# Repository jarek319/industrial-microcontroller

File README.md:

# industrial-microcontroller
A familiar platform designed for robust and unpredictable environments

I really like this project. I worked at a museum fabricator for a while, working on their electronic internals. I had an awesome time and I learned a lot about real-world applications and how to make a design that works perfectly on a lab bench work perfectly after being shipped around the world, plugged into the wrong power supply, kicked repeatedly and left in baking heat and 100% humidity.

Lots of isolation.

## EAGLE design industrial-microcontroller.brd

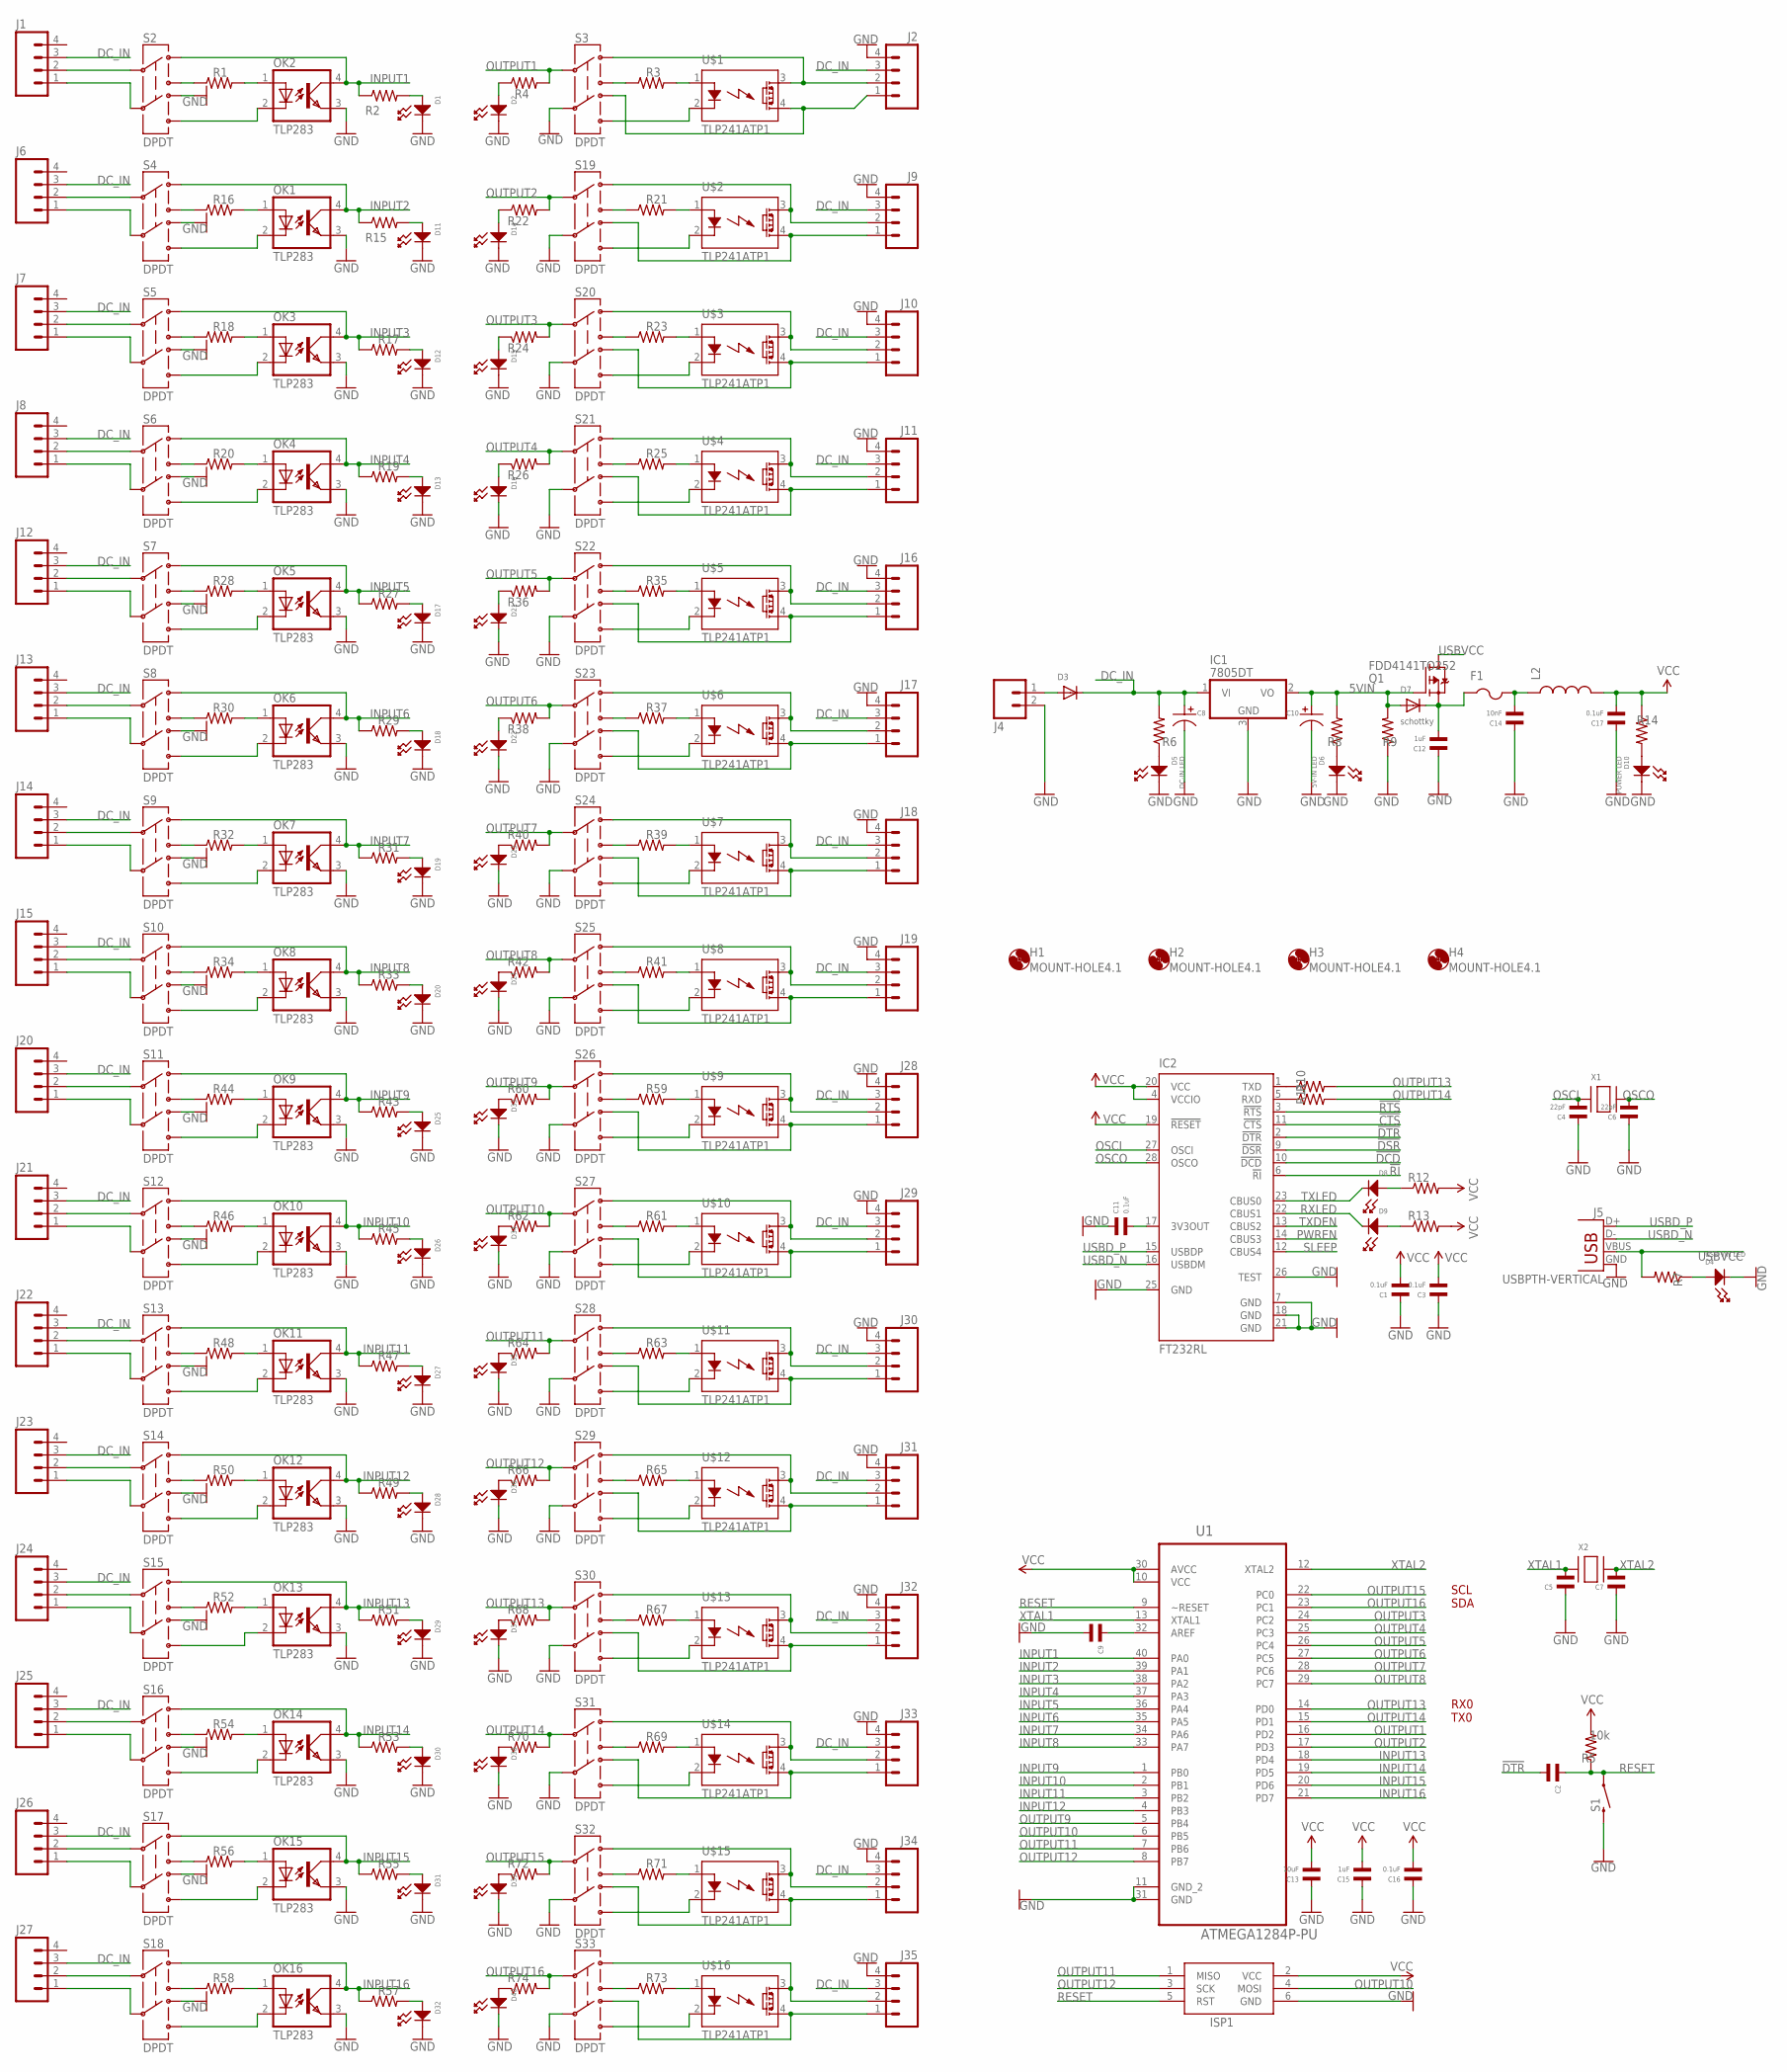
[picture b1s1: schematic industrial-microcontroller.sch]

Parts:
C1, C3, C11, C16, C17: 0.1uF; C0805
C2, C5, C7, C9: CAPACITOR_NP_0805; C0805
C4, C6: 22pF; C0805
C8, C10: CAPACITOR_P_10MM; CP10MM
C12, C15: 1uF; C0805
C13: 10uF; C0805
C14: 10nF; C0805
D1, D2, D8, D9, D11, D12, D13, D14, D15, D16, D17, D18, D19, D20, D21, D22, D23, D24, D25, D26, D27, D28, D29, D30, D31, D32, D33, D34, D35, D36, D37, D38, D39, D40: LED_SINGLE-0805; LED0805
D3: DIODESMA; SMADIODE
D4: USB-VIN LED; LED0805
D5: DC-IN LED; LED0805
D6: 5V-IN LED; LED0805
D7: schottky; SMADIODE
D10: POWER LED; LED0805
F1: PTCFUSE-1812; 1812
H1, H2, H3, H4: MOUNT-HOLE4.1; 4,1
IC1: 7805DT; TO252
IC2: FT232RL; SSOP28
ISP1: AVRISP-BOX
J1, J2, J6, J7, J8, J9, J10, J11, J12, J13, J14, J15, J16, J17, J18, J19, J20, J21, J22, J23, J24, J25, J26, J27, J28, J29, J30, J31, J32, J33, J34, J35: M04POLAR; MOLEX-1X4
J4: M02POLAR; MOLEX-1X2
J5: USBPTH-VERTICAL; USB-B-PTH-VERTICAL
L2: INDUCTORCR75_V2; CR75_V2
OK1, OK2, OK3, OK4, OK5, OK6, OK7, OK8, OK9, OK10, OK11, OK12, OK13, OK14, OK15, OK16: TLP283; MINI-FLAT-4
Q1: FDD4141TO252; TO252
R1, R2, R3, R4, R6, R7, R8, R9, R10, R11, R12, R13, R14, R15, R16, R17, R18, R19, R20, R21, R22, R23, R24, R25, R26, R27, R28, R29, R30, R31, R32, R33, R34, R35, R36, R37, R38, R39, R40, R41, R42, R43, R44, R45, R46, R47, R48, R49, R50, R51, R52, R53, R54, R55, R56, R57, R58, R59, R60, R61, R62, R63, R64, R65, R66, R67, R68, R69, R70, R71, R72, R73, R74: RESISTOR_0805; R0805
R5: 10k; R0805
S1: SWITCH-MOMENTARY-212MM; TACTILE-PTH-12MM
S2, S3, S4, S5, S6, S7, S8, S9, S10, S11, S12, S13, S14, S15, S16, S17, S18, S19, S20, S21, S22, S23, S24, S25, S26, S27, S28, S29, S30, S31, S32, S33: DPDT; JS202011JCON
U1: ATMEGA1284P-PU; DIP254P1524X483-40
U$1, U$2, U$3, U$4, U$5, U$6, U$7, U$8, U$9, U$10, U$11, U$12, U$13, U$14, U$15, U$16: TLP241ATP1; TLP241A-TP1
X1, X2: XTAL-3.2X1.5; XTAL3215

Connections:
5VIN: C10.P$1, D7.A, IC1.2 (VO), Q1.1 (G), R8.P$2, R9.P$2
!CTS: IC2.11 (!CTS)
!DCD: IC2.10 (!DCD)
!DSR: IC2.9 (!DSR)
!DTR: C2.P$2, IC2.2 (!DTR)
!RI: IC2.6 (!RI)
!RTS: IC2.3 (!RTS)
DC_IN: C8.P$1, D3.C, IC1.1 (VI), J1.3, J2.3, J6.3, J7.3, J8.3, J9.3, J10.3, J11.3, J12.3, J13.3, J14.3, J15.3, J16.3, J17.3, J18.3, J19.3, J20.3, J21.3, J22.3, J23.3, J24.3, J25.3, J26.3, J27.3, J28.3, J29.3, J30.3, J31.3, J32.3, J33.3, J34.3, J35.3, R6.P$2
GND: C1.P$1, C3.P$1, C4.P$1, C5.P$1, C6.P$1, C7.P$1, C8.P$2, C9.P$2, C10.P$2, C11.P$1, C12.P$1, C13.P$1, C14.P$1, C15.P$1, C16.P$1, C17.P$1, D1.CATHODE, D2.CATHODE, D4.CATHODE, D5.CATHODE, D6.CATHODE, D10.CATHODE, D11.CATHODE, D12.CATHODE, D13.CATHODE, D14.CATHODE, D15.CATHODE, D16.CATHODE, D17.CATHODE, D18.CATHODE, D19.CATHODE, D20.CATHODE, D21.CATHODE, D22.CATHODE, D23.CATHODE, D24.CATHODE, D25.CATHODE, D26.CATHODE, D27.CATHODE, D28.CATHODE, D29.CATHODE, D30.CATHODE, D31.CATHODE, D32.CATHODE, D33.CATHODE, D34.CATHODE, D35.CATHODE, D36.CATHODE, D37.CATHODE, D38.CATHODE, D39.CATHODE, D40.CATHODE, IC1.3 (GND), IC2.7 (GND), IC2.18 (GND), IC2.21 (GND), IC2.25 (GND), IC2.26 (TEST), ISP1.6 (GND), J2.4, J4.2, J5.GND, J9.4, J10.4, J11.4, J16.4, J17.4, J18.4, J19.4, J28.4, J29.4, J30.4, J31.4, J32.4, J33.4, J34.4, J35.4, OK1.3 (EMIT), OK2.3 (EMIT), OK3.3 (EMIT), OK4.3 (EMIT), OK5.3 (EMIT), OK6.3 (EMIT), OK7.3 (EMIT), OK8.3 (EMIT), OK9.3 (EMIT), OK10.3 (EMIT), OK11.3 (EMIT), OK12.3 (EMIT), OK13.3 (EMIT), OK14.3 (EMIT), OK15.3 (EMIT), OK16.3 (EMIT), R9.P$1, S1.3 (2), S2.4, S3.5, S4.4, S5.4, S6.4, S7.4, S8.4, S9.4, S10.4, S11.4, S12.4, S13.4, S14.4, S15.4, S16.4, S17.4, S18.4, S19.5, S20.5, S21.5, S22.5, S23.5, S24.5, S25.5, S26.5, S27.5, S28.5, S29.5, S30.5, S31.5, S32.5, S33.5, U1.11 (GND_2), U1.31 (GND)
INPUT1: OK2.4 (COL), R2.P$1, S2.1, U1.40 (PA0)
INPUT2: OK1.4 (COL), R15.P$1, S4.1, U1.39 (PA1)
INPUT3: OK3.4 (COL), R17.P$1, S5.1, U1.38 (PA2)
INPUT4: OK4.4 (COL), R19.P$1, S6.1, U1.37 (PA3)
INPUT5: OK5.4 (COL), R27.P$1, S7.1, U1.36 (PA4)
INPUT6: OK6.4 (COL), R29.P$1, S8.1, U1.35 (PA5)
INPUT7: OK7.4 (COL), R31.P$1, S9.1, U1.34 (PA6)
INPUT8: OK8.4 (COL), R33.P$1, S10.1, U1.33 (PA7)
INPUT9: OK9.4 (COL), R43.P$1, S11.1, U1.1 (PB0)
INPUT10: OK10.4 (COL), R45.P$1, S12.1, U1.2 (PB1)
INPUT11: OK11.4 (COL), R47.P$1, S13.1, U1.3 (PB2)
INPUT12: OK12.4 (COL), R49.P$1, S14.1, U1.4 (PB3)
INPUT13: OK13.4 (COL), R51.P$1, S15.1, U1.18 (PD4)
INPUT14: OK14.4 (COL), R53.P$1, S16.1, U1.19 (PD5)
INPUT15: OK15.4 (COL), R55.P$1, S17.1, U1.20 (PD6)
INPUT16: OK16.4 (COL), R57.P$1, S18.1, U1.21 (PD7)
unnamed: D5.ANODE, R6.P$1
unnamed: D1.ANODE, R2.P$2
unnamed: D6.ANODE, R8.P$1
unnamed: C14.P$2, F1.2, L2.P$1 (1)
unnamed: D10.ANODE, R14.P$2
unnamed: D3.A, J4.1
unnamed: D4.ANODE, R7.P$1
unnamed: D11.ANODE, R15.P$2
unnamed: R18.P$1, S5.3
unnamed: R3.P$2, U$1.1 (A)
unnamed: R20.P$1, S6.3
unnamed: OK1.1 (A), R16.P$2
unnamed: D12.ANODE, R17.P$2
unnamed: R28.P$1, S7.3
unnamed: R30.P$1, S8.3
unnamed: OK3.1 (A), R18.P$2
unnamed: D2.ANODE, R4.P$1
unnamed: D13.ANODE, R19.P$2
unnamed: R32.P$1, S9.3
unnamed: OK2.2 (C), S2.6
unnamed: R34.P$1, S10.3
unnamed: OK4.1 (A), R20.P$2
unnamed: R1.P$1, S2.3
unnamed: D14.ANODE, R22.P$1
unnamed: J9.2, S19.1, U$2.3 (DS1)
unnamed: OK2.1 (A), R1.P$2
unnamed: J9.1, S19.4, U$2.4 (DS2)
unnamed: R21.P$2, U$2.1 (A)
unnamed: D15.ANODE, R24.P$1
unnamed: J10.2, S20.1, U$3.3 (DS1)
unnamed: J10.1, S20.4, U$3.4 (DS2)
unnamed: R23.P$2, U$3.1 (A)
unnamed: D16.ANODE, R26.P$1
unnamed: J11.2, S21.1, U$4.3 (DS1)
unnamed: J2.2, S3.1, U$1.3 (DS1)
unnamed: J11.1, S21.4, U$4.4 (DS2)
unnamed: R25.P$2, U$4.1 (A)
unnamed: J2.1, S3.4, U$1.4 (DS2)
unnamed: D17.ANODE, R27.P$2
unnamed: R44.P$1, S11.3
unnamed: R46.P$1, S12.3
unnamed: OK5.1 (A), R28.P$2
unnamed: D18.ANODE, R29.P$2
unnamed: R48.P$1, S13.3
unnamed: R50.P$1, S14.3
unnamed: OK6.1 (A), R30.P$2
unnamed: D19.ANODE, R31.P$2
unnamed: R52.P$1, S15.3
unnamed: R54.P$1, S16.3
unnamed: C11.P$2, IC2.17 (3V3OUT)
unnamed: OK7.1 (A), R32.P$2
unnamed: D20.ANODE, R33.P$2
unnamed: D8.ANODE, R12.P$1
unnamed: R56.P$1, S17.3
unnamed: D9.ANODE, R13.P$1
unnamed: IC2.1 (TXD), R10.P$1
unnamed: IC2.5 (RXD), R11.P$1
unnamed: R58.P$1, S18.3
unnamed: OK8.1 (A), R34.P$2
unnamed: C9.P$1, U1.32 (AREF)
unnamed: D21.ANODE, R36.P$1
unnamed: J16.2, S22.1, U$5.3 (DS1)
unnamed: J16.1, S22.4, U$5.4 (DS2)
unnamed: C12.P$2, D7.C, F1.1, Q1.2 (S)
unnamed: R35.P$2, U$5.1 (A)
unnamed: D22.ANODE, R38.P$1
unnamed: J17.2, S23.1, U$6.3 (DS1)
unnamed: J17.1, S23.4, U$6.4 (DS2)
unnamed: R37.P$2, U$6.1 (A)
unnamed: D23.ANODE, R40.P$1
unnamed: J18.2, S24.1, U$7.3 (DS1)
unnamed: J18.1, S24.4, U$7.4 (DS2)
unnamed: R39.P$2, U$7.1 (A)
unnamed: D24.ANODE, R42.P$1
unnamed: J19.2, S25.1, U$8.3 (DS1)
unnamed: J19.1, S25.4, U$8.4 (DS2)
unnamed: R41.P$2, U$8.1 (A)
unnamed: D25.ANODE, R43.P$2
unnamed: R16.P$1, S4.3
unnamed: J6.2, S4.2
unnamed: OK9.1 (A), R44.P$2
unnamed: D26.ANODE, R45.P$2
unnamed: J6.1, S4.5
unnamed: J7.1, S5.5
unnamed: OK10.1 (A), R46.P$2
unnamed: D27.ANODE, R47.P$2
unnamed: J7.2, S5.2
unnamed: OK1.2 (C), S4.6
unnamed: OK11.1 (A), R48.P$2
unnamed: D28.ANODE, R49.P$2
unnamed: OK3.2 (C), S5.6
unnamed: J8.2, S6.2
unnamed: OK12.1 (A), R50.P$2
unnamed: D29.ANODE, R51.P$2
unnamed: J8.1, S6.5
unnamed: OK4.2 (C), S6.6
unnamed: OK13.1 (A), R52.P$2
unnamed: D30.ANODE, R53.P$2
unnamed: J12.2, S7.2
unnamed: J12.1, S7.5
unnamed: OK14.1 (A), R54.P$2
unnamed: D31.ANODE, R55.P$2
unnamed: OK5.2 (C), S7.6
unnamed: OK6.2 (C), S8.6
unnamed: OK15.1 (A), R56.P$2
unnamed: D32.ANODE, R57.P$2
unnamed: J13.2, S8.2
unnamed: J13.1, S8.5
unnamed: OK16.1 (A), R58.P$2
unnamed: D33.ANODE, R60.P$1
unnamed: J28.2, S26.1, U$9.3 (DS1)
unnamed: J28.1, S26.4, U$9.4 (DS2)
unnamed: R59.P$2, U$9.1 (A)
unnamed: D34.ANODE, R62.P$1
unnamed: J29.2, S27.1, U$10.3 (DS1)
unnamed: J29.1, S27.4, U$10.4 (DS2)
unnamed: R61.P$2, U$10.1 (A)
unnamed: D35.ANODE, R64.P$1
unnamed: J30.2, S28.1, U$11.3 (DS1)
unnamed: J30.1, S28.4, U$11.4 (DS2)
unnamed: R63.P$2, U$11.1 (A)
unnamed: D36.ANODE, R66.P$1
unnamed: J31.2, S29.1, U$12.3 (DS1)
unnamed: J31.1, S29.4, U$12.4 (DS2)
unnamed: R65.P$2, U$12.1 (A)
unnamed: D37.ANODE, R68.P$1
unnamed: J32.2, S30.1, U$13.3 (DS1)
unnamed: J32.1, S30.4, U$13.4 (DS2)
unnamed: R67.P$2, U$13.1 (A)
unnamed: D38.ANODE, R70.P$1
unnamed: J33.2, S31.1, U$14.3 (DS1)
unnamed: J33.1, S31.4, U$14.4 (DS2)
unnamed: R69.P$2, U$14.1 (A)
unnamed: D39.ANODE, R72.P$1
unnamed: J34.2, S32.1, U$15.3 (DS1)
unnamed: J34.1, S32.4, U$15.4 (DS2)
unnamed: R71.P$2, U$15.1 (A)
unnamed: D40.ANODE, R74.P$1
unnamed: J35.2, S33.1, U$16.3 (DS1)
unnamed: J35.1, S33.4, U$16.4 (DS2)
unnamed: R73.P$2, U$16.1 (A)
unnamed: J1.2, S2.2
unnamed: J1.1, S2.5
unnamed: R3.P$1, S3.3
unnamed: S3.6, U$1.2 (K)
unnamed: J14.2, S9.2
unnamed: J14.1, S9.5
unnamed: OK7.2 (C), S9.6
unnamed: J15.2, S10.2
unnamed: J15.1, S10.5
unnamed: OK8.2 (C), S10.6
unnamed: J20.2, S11.2
unnamed: J20.1, S11.5
unnamed: OK9.2 (C), S11.6
unnamed: OK10.2 (C), S12.6
unnamed: J21.2, S12.2
unnamed: J21.1, S12.5
unnamed: J22.2, S13.2
unnamed: J22.1, S13.5
unnamed: OK11.2 (C), S13.6
unnamed: J23.2, S14.2
unnamed: OK12.2 (C), S14.6
unnamed: OK13.2 (C), S15.6
unnamed: J24.2, S15.2
unnamed: J24.1, S15.5
unnamed: J25.2, S16.2
unnamed: J25.1, S16.5
unnamed: OK14.2 (C), S16.6
unnamed: J26.2, S17.2
unnamed: J26.1, S17.5
unnamed: J27.2, S18.2
unnamed: J27.1, S18.5
unnamed: OK15.2 (C), S17.6
unnamed: OK16.2 (C), S18.6
unnamed: R21.P$1, S19.3
unnamed: R23.P$1, S20.3
unnamed: S19.6, U$2.2 (K)
unnamed: S20.6, U$3.2 (K)
unnamed: R25.P$1, S21.3
unnamed: S21.6, U$4.2 (K)
unnamed: R35.P$1, S22.3
unnamed: S22.6, U$5.2 (K)
unnamed: R37.P$1, S23.3
unnamed: S23.6, U$6.2 (K)
unnamed: R39.P$1, S24.3
unnamed: S24.6, U$7.2 (K)
unnamed: R41.P$1, S25.3
unnamed: S25.6, U$8.2 (K)
unnamed: R59.P$1, S26.3
unnamed: S26.6, U$9.2 (K)
unnamed: R61.P$1, S27.3
unnamed: S27.6, U$10.2 (K)
unnamed: R63.P$1, S28.3
unnamed: S28.6, U$11.2 (K)
unnamed: R65.P$1, S29.3
unnamed: S29.6, U$12.2 (K)
unnamed: R67.P$1, S30.3
unnamed: S30.6, U$13.2 (K)
unnamed: R69.P$1, S31.3
unnamed: S31.6, U$14.2 (K)
unnamed: R71.P$1, S32.3
unnamed: S32.6, U$15.2 (K)
unnamed: R73.P$1, S33.3
unnamed: S33.6, U$16.2 (K)
OSCI: C4.P$2, IC2.27 (OSCI), X1.P$1
OSCO: C6.P$2, IC2.28 (OSCO), X1.P$2
OUTPUT1: R4.P$2, S3.2, U1.16 (PD2)
OUTPUT2: R22.P$2, S19.2, U1.17 (PD3)
OUTPUT3: R24.P$2, S20.2, U1.24 (PC2)
OUTPUT4: R26.P$2, S21.2, U1.25 (PC3)
OUTPUT5: R36.P$2, S22.2, U1.26 (PC4)
OUTPUT6: R38.P$2, S23.2, U1.27 (PC5)
OUTPUT7: R40.P$2, S24.2, U1.28 (PC6)
OUTPUT8: R42.P$2, S25.2, U1.29 (PC7)
OUTPUT9: R60.P$2, S26.2, U1.5 (PB4)
OUTPUT10: ISP1.4 (MOSI), R62.P$2, S27.2, U1.6 (PB5)
OUTPUT11: ISP1.1 (MISO), R64.P$2, S28.2, U1.7 (PB6)
OUTPUT12: ISP1.3 (SCK), R66.P$2, S29.2, U1.8 (PB7)
OUTPUT13: R10.P$2, R68.P$2, S30.2, U1.14 (PD0)
OUTPUT14: R11.P$2, R70.P$2, S31.2, U1.15 (PD1)
OUTPUT15: R72.P$2, S32.2, U1.22 (PC0)
OUTPUT16: R74.P$2, S33.2, U1.23 (PC1)
PWREN: IC2.14 (CBUS3)
RESET: C2.P$1, ISP1.5 (RST), R5.P$1, S1.1, U1.9 (~RESET)
RXLED: D9.CATHODE, IC2.22 (CBUS1)
SLEEP: IC2.12 (CBUS4)
TXDEN: IC2.13 (CBUS2)
TXLED: D8.CATHODE, IC2.23 (CBUS0)
USBD_N: IC2.16 (USBDM), J5.D-
USBD_P: IC2.15 (USBDP), J5.D+
USBVCC: J5.VBUS, Q1.3 (D), R7.P$2
VCC: C1.P$2, C3.P$2, C13.P$2, C15.P$2, C16.P$2, C17.P$2, IC2.4 (VCCIO), IC2.19 (!RESET), IC2.20 (VCC), ISP1.2 (VCC), L2.P$2 (2), R5.P$2, R12.P$2, R13.P$2, R14.P$1, U1.10 (VCC), U1.30 (AVCC)
XTAL1: C5.P$2, U1.13 (XTAL1), X2.P$1
XTAL2: C7.P$2, U1.12 (XTAL2), X2.P$2

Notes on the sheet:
RX0 TX0
SCL SDA

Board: 2 copper layers, 243 parts (124 on the bottom side), 251 nets, no tracks yet.

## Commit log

2018-07-05 design in progress

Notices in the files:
parts and their libraries:
SparkFun-Connectors: Licensing: Creative Commons ShareAlike 4.0 International - https://creativecommons.org/licenses/by-sa/4.0
